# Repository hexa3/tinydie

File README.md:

tinydie

its a dice that lights up!!! you press the button and the lights go all crazy like its rolling and then when u let go it slows down and stops on a number 1 to 6. its so cool

the brain is a tiny chip called ATtiny412 it only has 8 legs but its really smart. when nobody plays with it it goes to sleep so the battery lasts forever (not actually forever but like a really long time) so theres no on off switch you dont need one

how i made it step by step (with pictures): https://sheheryar.xyz/tinydie-board/journal/

| thing | what it is |
|---|---|
| brain chip | ATtiny412-SSNR (8 legs) |
| how big | 45mm x 45mm its like a cookie |
| battery | CR2032 coin battery its on the back |
| made in | KiCad 10 |
| how much $$ | like $1.75 for one dice. or $15 to $31 for 5 of them with the boards and shipping, look in BOM.md |
| mistakes | 0!! i checked |

how it works

ok so a dice has 6 sides right. but you only need 4 groups of lights because the dots always come in pairs like the top left one and the bottom right one are always on together. the middle one is by itself tho

| group | leg on chip | which lights | on for |
|---|---|---|---|
| A | PA1 (leg 4) | top left + bottom right | 2 3 4 5 6 |
| B | PA2 (leg 5) | top right + bottom left | 4 5 6 |
| C | PA3 (leg 7) | middle left + middle right | 6 |
| D | PA6 (leg 2) | middle | 1 3 5 |

the chip has 6 legs you can use. 4 are for lights 1 is the button (PA7 leg 3) and 1 is for putting the program on (PA0 leg 6). so every leg has a job lol

every light has a resistor thats 330 ohms its like a speed bump so the light doesnt get too much power. each light uses 3mA so even a 6 is only 18mA

how does it pick the number?? theres a clock in the chip that counts super super fast and when you hold the button it looks at the clock. nobody can hold it for the exact same time twice so its always a surprise :)

battery: one roll is like 5 seconds and the battery can do about 10000 rolls!!! when its sleeping it uses basically nothing

whats in here

| folder/file | whats in it |
|---|---|
| firmware/ | the program for the chip its in C |
| hardware/tinydie.kicad_pro | the kicad project open this one in KiCad 10 |
| hardware/tinydie.kicad_sch | the schematic (the drawing of how stuff connects) |
| hardware/tinydie.kicad_pcb | the board |
| hardware/fab/ | the files u send to the factory + parts list |
| BOM.md | shopping list |

putting the program on the chip

| step | type this | u need |
|---|---|---|
| 1 | cd firmware | nothing |
| 2 | make | avr-gcc and avr-libc (arch linux: pacman -S avr-gcc avr-libc) |
| 3 | make flash | pymcuprog (pip install pymcuprog) and a usb serial thing |

the program is only 447 bytes and the chip fits 4096 so theres LOTS of room

the usb serial thing has to be 3.3V. plug the wires like this

| usb thing pin | goes to |
|---|---|
| TX | 1k ohm resistor then J1 "U" |
| RX | J1 "U" too (the chip side of the resistor) |
| 3V3 | J1 "V" |
| GND | J1 "G" |

TAKE THE BATTERY OUT BEFORE YOU PLUG IN THE 3V3 WIRE!!! really dont forget

how to make one

| step | what to do |
|---|---|
| 1 | send hardware/fab/tinydie-gerbers.zip to a board factory. pick 2 layers 1.6mm thick and any colour u want. its not hard to make so any factory can do it |
| 2 | buy the stuff in BOM.md |
| 3 | solder the front first. U1, C1, R1 to R7, D1 to D7 and SW1. the little mark on the lights goes to the left side |
| 4 | solder J1 |
| 5 | then the battery holder on the back last |

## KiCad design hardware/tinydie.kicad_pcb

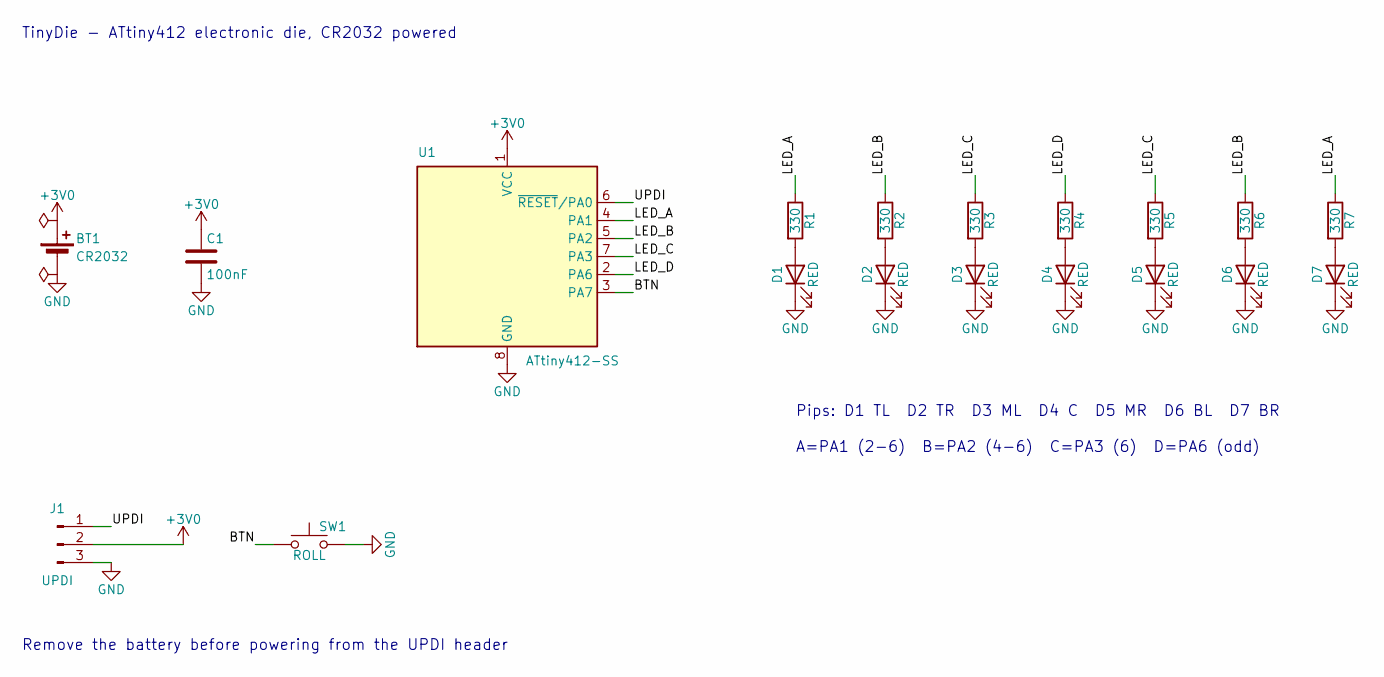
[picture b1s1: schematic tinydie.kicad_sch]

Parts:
BT1: CR2032; BatteryHolder_MYOUNG_BS-07-A1BJ001_CR2032; MPN MYOUNG BS-07-A1BJ001
C1: 100nF; C_0805_2012Metric_Pad1.18x1.45mm_HandSolder; MPN 0805 100nF X7R 16V (generic)
D1, D2, D3, D4, D5, D6, D7: RED; LED_0805_2012Metric_Pad1.15x1.40mm_HandSolder; MPN 0805 red LED, Vf~2.0V (generic)
J1: UPDI; PinHeader_1x03_P2.54mm_Vertical; MPN 1x3 2.54mm pin header (generic)
R1, R2, R3, R4, R5, R6, R7: 330; R_0805_2012Metric_Pad1.20x1.40mm_HandSolder; MPN 0805 330R 1% (generic)
SW1: ROLL; SW_PUSH_6mm; MPN 6x6mm THT tactile switch, 4-pin (generi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
U1: ATtiny412-SS; SOIC-8_3.9x4.9mm_P1.27mm; MPN Microchip ATTINY412-SSNR

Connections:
+3V0: BT1.1 (+), C1.1, J1.2, U1.1 (VCC)
/BTN: SW1.1, U1.3 (PA7)
/LED_A: R1.1, R7.1, U1.4 (PA1)
/LED_B: R2.1, R6.1, U1.5 (PA2)
/LED_C: R3.1, R5.1, U1.7 (PA3)
/LED_D: R4.1, U1.2 (PA6)
/UPDI: J1.1, U1.6 (~RESET/PA0)
GND: BT1.2 (-), C1.2, D1.1 (K), D2.1 (K), D3.1 (K), D4.1 (K), D5.1 (K), D6.1 (K), D7.1 (K), J1.3, SW1.2, U1.8 (GND)
unnamed: D1.2 (A), R1.2
unnamed: D2.2 (A), R2.2
unnamed: D3.2 (A), R3.2
unnamed: D4.2 (A), R4.2
unnamed: D5.2 (A), R5.2
unnamed: D6.2 (A), R6.2
unnamed: D7.2 (A), R7.2

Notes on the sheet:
TinyDie - ATtiny412 electronic die, CR2032 powered
Pips: D1 TL D2 TR D3 ML D4 C D5 MR D6 BL D7 BR
A=PA1 (2-6) B=PA2 (4-6) C=PA3 (6) D=PA6 (odd)
Remove the battery before powering from the UPDI header

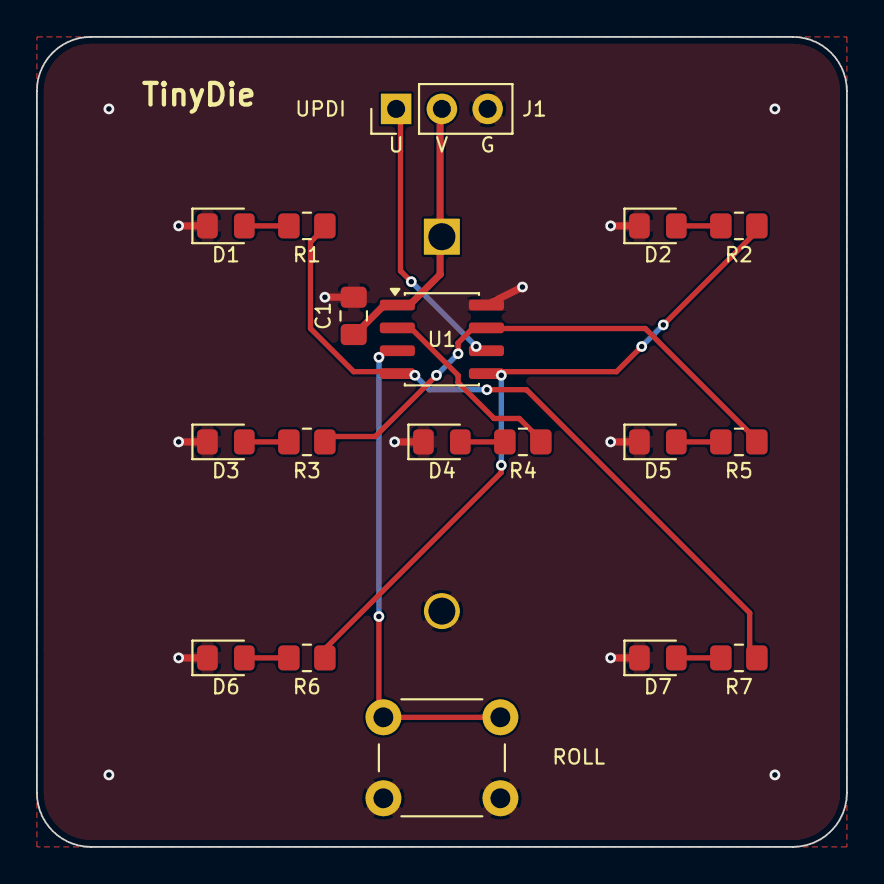
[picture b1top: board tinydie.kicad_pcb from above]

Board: 2 copper layers, 45.0 x 45.0 mm, 19 parts (1 on the bottom side), 15 nets.

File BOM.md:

tinydie shoping list

this is all the stuff u need to buy to make the dice and how much it costs. the rule was dont spend more than $35 for everything (parts and boards and shipping)

the prices are guesses from like late 2026 from LCSC and JLCPCB so check them again before u buy ok. shipping is different depending where you live

stuff for one dice

| name on board | how many | what is it | the exact one | footprint | how much each (ish) |
|---|---|---|---|---|---|
| U1 | 1 | the brain chip | Microchip ATTINY412-SSNR | SOIC-8 | $0.75 |
| BT1 | 1 | battery holder (on the back) | MYOUNG BS-07-A1BJ001 | BatteryHolder_MYOUNG_BS-07-A1BJ001_CR2032 | $0.15 |
| - | 1 | CR2032 battery | any | - | $0.40 |
| D1 to D7 | 7 | red lights | 0805, 2.0V | LED_0805 | $0.03 |
| R1 to R7 | 7 | 330 ohm resistor one for every light | 0805 | R_0805 | $0.01 |
| C1 | 1 | 100nF capacitor it keeps the power smooth for the chip | 0805, X7R, 16V or more | C_0805 | $0.01 |
| SW1 | 1 | the button 6mm x 6mm | any | SW_PUSH_6mm | $0.08 |
| J1 | 1 | 3 pins for putting the program on | 2.54mm pin header | PinHeader_1x03_P2.54mm | $0.03 |

one dice is like $1.75 thats so cheap

buying for 5 dice

some stuff only comes in big packs so u get extras (bonus!!)

| what | how much (ish) |
|---|---|
| 5 brain chips | $3.75 |
| 5 battery holders | $0.75 |
| 5 batteries | $2.00 |
| 50 red lights (smallest pack they have) | $1.00 |
| 100 resistors | $0.30 |
| 50 capacitors | $0.30 |
| 5 buttons | $0.40 |
| 1 strip of 40 pins (snap off 3) | $0.30 |
| all the parts | like $8.80 |
| 5 boards (45mm x 45mm, 2 layers, 1.6mm) | like $2.00 |
| shipping boards | $2 to $10 |
| shipping parts | $2 to $10 |
| EVERYTHING | like $15 to $31 |

if u dont have one u also need a usb serial thing (CH340 or CP2102) to put the program on. its like $2 and u need one 1k ohm resistor with it. even if everything costs the most it can its like $33 so still under $35 yay

if its too expensive

| try this | why |
|---|---|
| buy the parts from the same place that makes the boards | then u only pay shipping once |
| get the cheapest 0805 lights and resistors | any 0805 ones fit |
| buy batteries from a store near u | theyre the most expensive small thing |

kicad also made its own parts list its in hardware/fab/tinydie-bom.csv

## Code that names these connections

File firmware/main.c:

/*
 * TinyDie firmware - ATtiny412, CR2032-powered electronic die.
 *
 * Pinout (SOIC-8):
 *   1 VDD   2 PA6 -> LED group D (centre)
 *   3 PA7 <- button (to GND, internal pull-up)
 *   4 PA1 -> LED group A (top-left + bottom-right)
 *   5 PA2 -> LED group B (top-right + bottom-left)
 *   6 PA0  = UPDI (programming)
 *   7 PA3 -> LED group C (middle-left + middle-right)
 *   8 GND
 *
 * Press the button: the die rolls while held, slows down on release,
 * shows the result for a few seconds, then enters power-down sleep
 * (~0.1 uA) until the next press. No power switch needed.
 */
#define F_CPU 3333333UL /* default: 20 MHz / 6 */

#include <avr/io.h>
#include <avr/interrupt.h>
#include <avr/sleep.h>
#include <util/delay.h>

#define LA PIN1_bm
#define LB PIN2_bm
#define LC PIN3_bm
#define LD PIN6_bm
#define LED_MASK (LA | LB | LC | LD)
#define BTN PIN7_bm

#define SHOW_MS 4000u

static const uint8_t face[7] = {
    0,
    LD,                /* 1 */
    LA,                /* 2 */
    LA | LD,           /* 3 */
    LA | LB,           /* 4 */
    LA | LB | LD,      /* 5 */
    LA | LB | LC,      /* 6 */
};

static uint16_t rng = 0xACE1;

static uint8_t roll(void)
{
    uint8_t v;
    do { /* xorshift16, rejection-sample 3 bits to 1..6 */
        rng ^= rng << 7;
        rng ^= rng >> 9;
        rng ^= rng << 8;
        v = rng & 7;
    } while (v > 5);
    return v + 1;
}

static void show(uint8_t n)
{
    PORTA.OUT = (PORTA.OUT & ~LED_MASK) | face[n];
}

static inline uint8_t pressed(void) { return !(PORTA.IN & BTN); }

static void delay_ms(uint16_t ms)
{
    while (ms--) _delay_ms(1);
}

ISR(PORTA_PORT_vect)
{
    PORTA.INTFLAGS = BTN; /* wake only */
}

int main(void)
{
    PORTA.DIRSET = LED_MASK;
    PORTA.OUTCLR = LED_MASK;
    PORTA.PIN7CTRL = PORT_PULLUPEN_bm | PORT_ISC_BOTHEDGES_gc;

    /* Free-running timer: its count at the moment of release seeds the RNG. */
    TCA0.SINGLE.CTRLA = TCA_SINGLE_ENABLE_bm;

    set_sleep_mode(SLEEP_MODE_PWR_DOWN);
    sei();

    /* Power-on self test: light every face once. */
    for (uint8_t i = 1; i <= 6; i++) { show(i); delay_ms(120); }
    show(0);

    for (;;) {
        if (pressed()) {
            /* Rolling while held. */
            while (pressed()) {
                rng ^= TCA0.SINGLE.CNT;
                if (!rng) rng = 0xACE1;
                show(roll());
                delay_ms(50);
            }
            delay_ms(20); /* debounce release */

            /* Slow down. */
            for (uint16_t d = 40; d < 300; d += d / 4) {
                show(roll());
                delay_ms(d);
            }
            show(roll());

            /* Hold the result, abort early on a new press. */
            for (uint16_t t = 0; t < SHOW_MS / 10 && !pressed(); t++)
                delay_ms(10);
            if (pressed()) continue;
        }

        show(0);
        sleep_enable();
        sleep_cpu(); /* wakes on button edge */
        sleep_disable();
        delay_ms(20); /* debounce press */
    }
}
